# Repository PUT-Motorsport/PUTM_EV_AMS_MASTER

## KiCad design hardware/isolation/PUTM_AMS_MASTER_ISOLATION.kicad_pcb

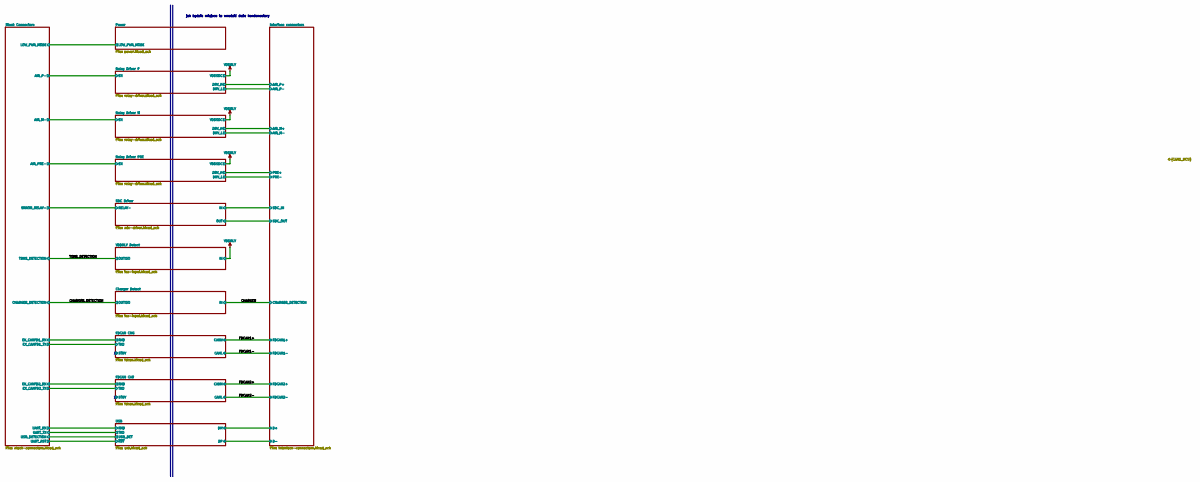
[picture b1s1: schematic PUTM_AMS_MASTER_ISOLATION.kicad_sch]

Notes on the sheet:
jak będzie miejsce to wsadzić duże kondensatory

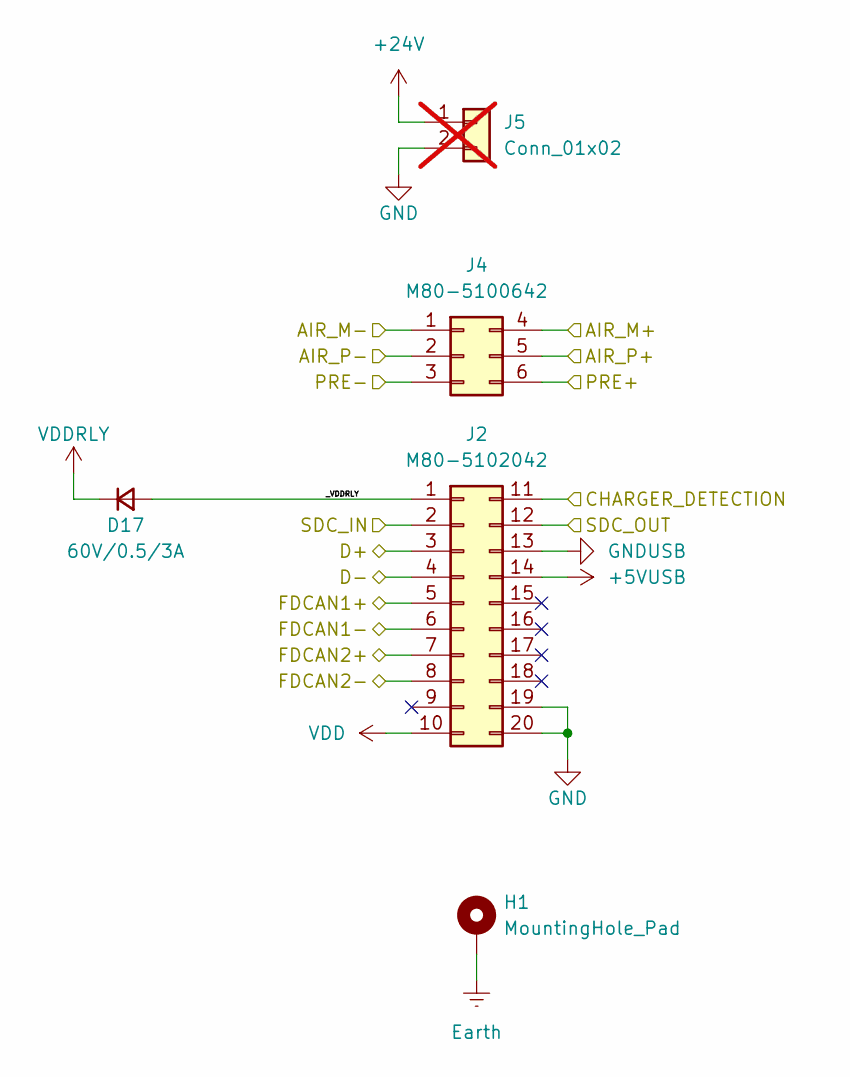
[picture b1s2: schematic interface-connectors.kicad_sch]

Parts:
D17: 60V/0.5/3A; D_SOD-123; Mouser Part Number 637-SKL36
H1: MountingHole_Pad; MountingHole_3.2mm_M3_Pad_Via
J2: M80-5102042; M80-51020YY; Mouser Part Number 855-M80-5102042
J4: M80-5100642; M80-51006YY; Mouser Part Number 855-M80-5100642
J5: Conn_01x02; PinHeader_1x02_P2.00mm_Vertical; not fitted

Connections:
+5VUSB: J2.14; also elsewhere on the board
+24V: J5.1; also elsewhere on the board
/CHARGER: J2.11; also elsewhere on the board
/FDCAN1+: J2.5; also elsewhere on the board
/FDCAN1-: J2.6; also elsewhere on the board
/FDCAN2+: J2.7; also elsewhere on the board
/FDCAN2-: J2.8; also elsewhere on the board
/Interface connectors/AIR_M+: J4.4; also elsewhere on the board
/Interface connectors/AIR_M-: J4.1; also elsewhere on the board
/Interface connectors/AIR_P+: J4.5; also elsewhere on the board
/Interface connectors/AIR_P-: J4.2; also elsewhere on the board
/Interface connectors/D+: J2.3; also elsewhere on the board
/Interface connectors/D-: J2.4; also elsewhere on the board
/Interface connectors/PRE+: J4.6; also elsewhere on the board
/Interface connectors/PRE-: J4.3; also elsewhere on the board
/Interface connectors/SDC_IN: J2.2; also elsewhere on the board
/Interface connectors/SDC_OUT: J2.12; also elsewhere on the board
/Interface connectors/_VDDRLY: D17.2 (A), J2.1
GND: J2.19, J2.20, J5.2; also elsewhere on the board
GNDUSB: J2.13; also elsewhere on the board
VDD: J2.10; also elsewhere on the board
VDDRLY: D17.1 (K); also elsewhere on the board

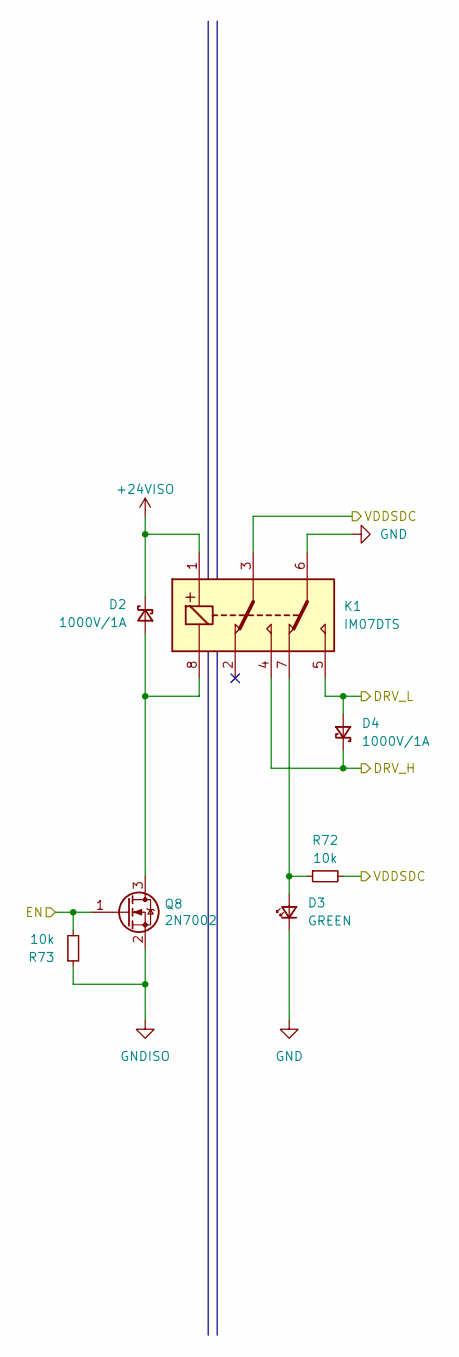
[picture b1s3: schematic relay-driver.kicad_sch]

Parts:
D2, D4: 1000V/1A; D_SOD-123; Mouser Part Number 863-NRVS1MFL
D3: GREEN; D_0603_1608Metric
K1: IM07DTS; IM23TS; Mouser Part Number 655-IM07DTS
Q8: 2N7002; SOT-23; Manufacturer_Part_Number --; Mouser Part Number 621-DMN65D8L-7
R72, R73: 10k; R_0603_1608Metric; Manufacturer_Part_Number --; Mouser Part Number --

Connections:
+24VISO: D2.1 (K), K1.1 (COIL_1); also elsewhere on the board
/Interface connectors/AIR_P+: D4.1 (K), K1.4 (NO_1); also elsewhere on the board
/Interface connectors/AIR_P-: D4.2 (A), K1.5 (NO_2); also elsewhere on the board
/Relay Driver P/EN: Q8.1 (G), R73.2; also elsewhere on the board
GND: D3.1 (K), K1.6 (COM_2); also elsewhere on the board
GNDISO: Q8.2 (S), R73.1; also elsewhere on the board
unnamed: D2.2 (A), K1.8 (COIL_2), Q8.3 (D)
unnamed: D3.2 (A), K1.7 (NC_2), R72.1
VDDRLY: K1.3 (COM_1), R72.2; also elsewhere on the board

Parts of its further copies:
D12, D15: GREEN; D_0603_1608Metric
K3, K4: IM07DTS; IM23TS; Mouser Part Number 655-IM07DTS
Q9, Q10: 2N7002; SOT-23; Manufacturer_Part_Number --; Mouser Part Number 621-DMN65D8L-7
R74, R83, R84, R85: 10k; R_0603_1608Metric; Manufacturer_Part_Number --; Mouser Part Number --

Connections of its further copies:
+24VISO: K3.1 (COIL_1), K4.1 (COIL_1); also elsewhere on the board
/Interface connectors/AIR_M+: K3.4 (NO_1); also elsewhere on the board
/Interface connectors/AIR_M-: K3.5 (NO_2); also elsewhere on the board
/Interface connectors/PRE+: K4.4 (NO_1); also elsewhere on the board
/Interface connectors/PRE-: K4.5 (NO_2); also elsewhere on the board
/Relay Driver M/EN: Q9.1 (G), R74.2; also elsewhere on the board
/Relay Driver PRE/EN: Q10.1 (G), R84.2; also elsewhere on the board
GND: D12.1 (K), D15.1 (K), K3.6 (COM_2), K4.6 (COM_2); also elsewhere on the board
GNDISO: Q9.2 (S), Q10.2 (S), R74.1, R84.1; also elsewhere on the board
unnamed 82: K3.8 (COIL_2), Q9.3 (D); also elsewhere on the board
unnamed: D12.2 (A), K3.7 (NC_2), R83.1
unnamed 84: K4.8 (COIL_2), Q10.3 (D); also elsewhere on the board
unnamed: D15.2 (A), K4.7 (NC_2), R85.1
VDDRLY: K3.3 (COM_1), K4.3 (COM_1), R83.2, R85.2; also elsewhere on the board

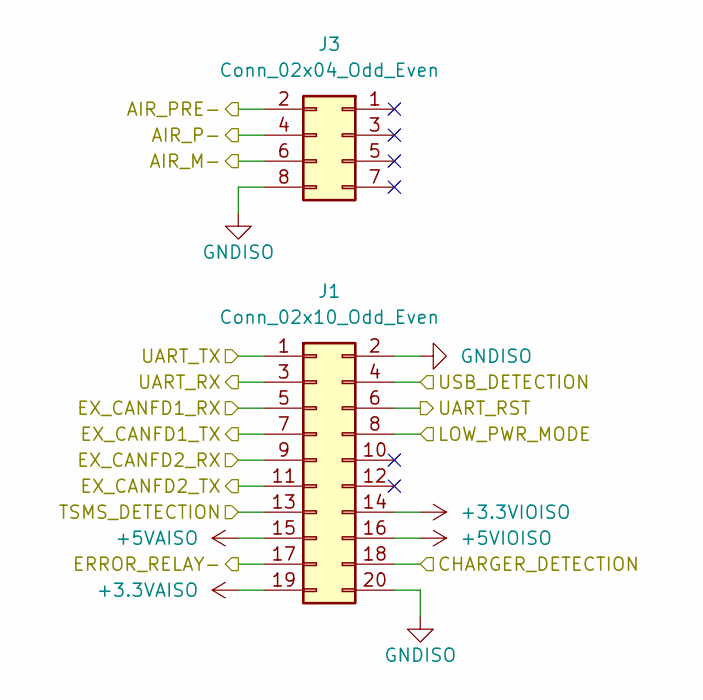
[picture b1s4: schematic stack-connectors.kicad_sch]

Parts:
J1: Conn_02x10_Odd_Even; PinSocket_2x10_P2.00mm_Vertical; Mouser Part Number 200-SQT12001LD
J3: Conn_02x04_Odd_Even; PinSocket_2x04_P2.00mm_Vertical; Mouser Part Number 200-SQT10801LD

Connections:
+3.3VAISO: J1.19; also elsewhere on the board
+3.3VIOISO: J1.14; also elsewhere on the board
+5VAISO: J1.15; also elsewhere on the board
+5VIOISO: J1.16; also elsewhere on the board
/CHARGER_DETECTION: J1.18; also elsewhere on the board
/FDCAN CAR/RXD: J1.9; also elsewhere on the board
/FDCAN CAR/TXD: J1.11; also elsewhere on the board
/FDCAN CHG/RXD: J1.5; also elsewhere on the board
/FDCAN CHG/TXD: J1.7; also elsewhere on the board
/Power/LOW_PWR_MODE: J1.8; also elsewhere on the board
/Relay Driver M/EN: J3.6; also elsewhere on the board
/Relay Driver P/EN: J3.4; also elsewhere on the board
/Relay Driver PRE/EN: J3.2; also elsewhere on the board
/SDC Driver/RELAY-: J1.17; also elsewhere on the board
/Stack Connectors/UART_RST: J1.6; also elsewhere on the board
/Stack Connectors/UART_RX: J1.3; also elsewhere on the board
/Stack Connectors/UART_TX: J1.1; also elsewhere on the board
/Stack Connectors/USB_DETECTION: J1.4; also elsewhere on the board
/TSMS_DETECTION: J1.13; also elsewhere on the board
GNDISO: J1.2, J1.20, J3.8; also elsewhere on the board

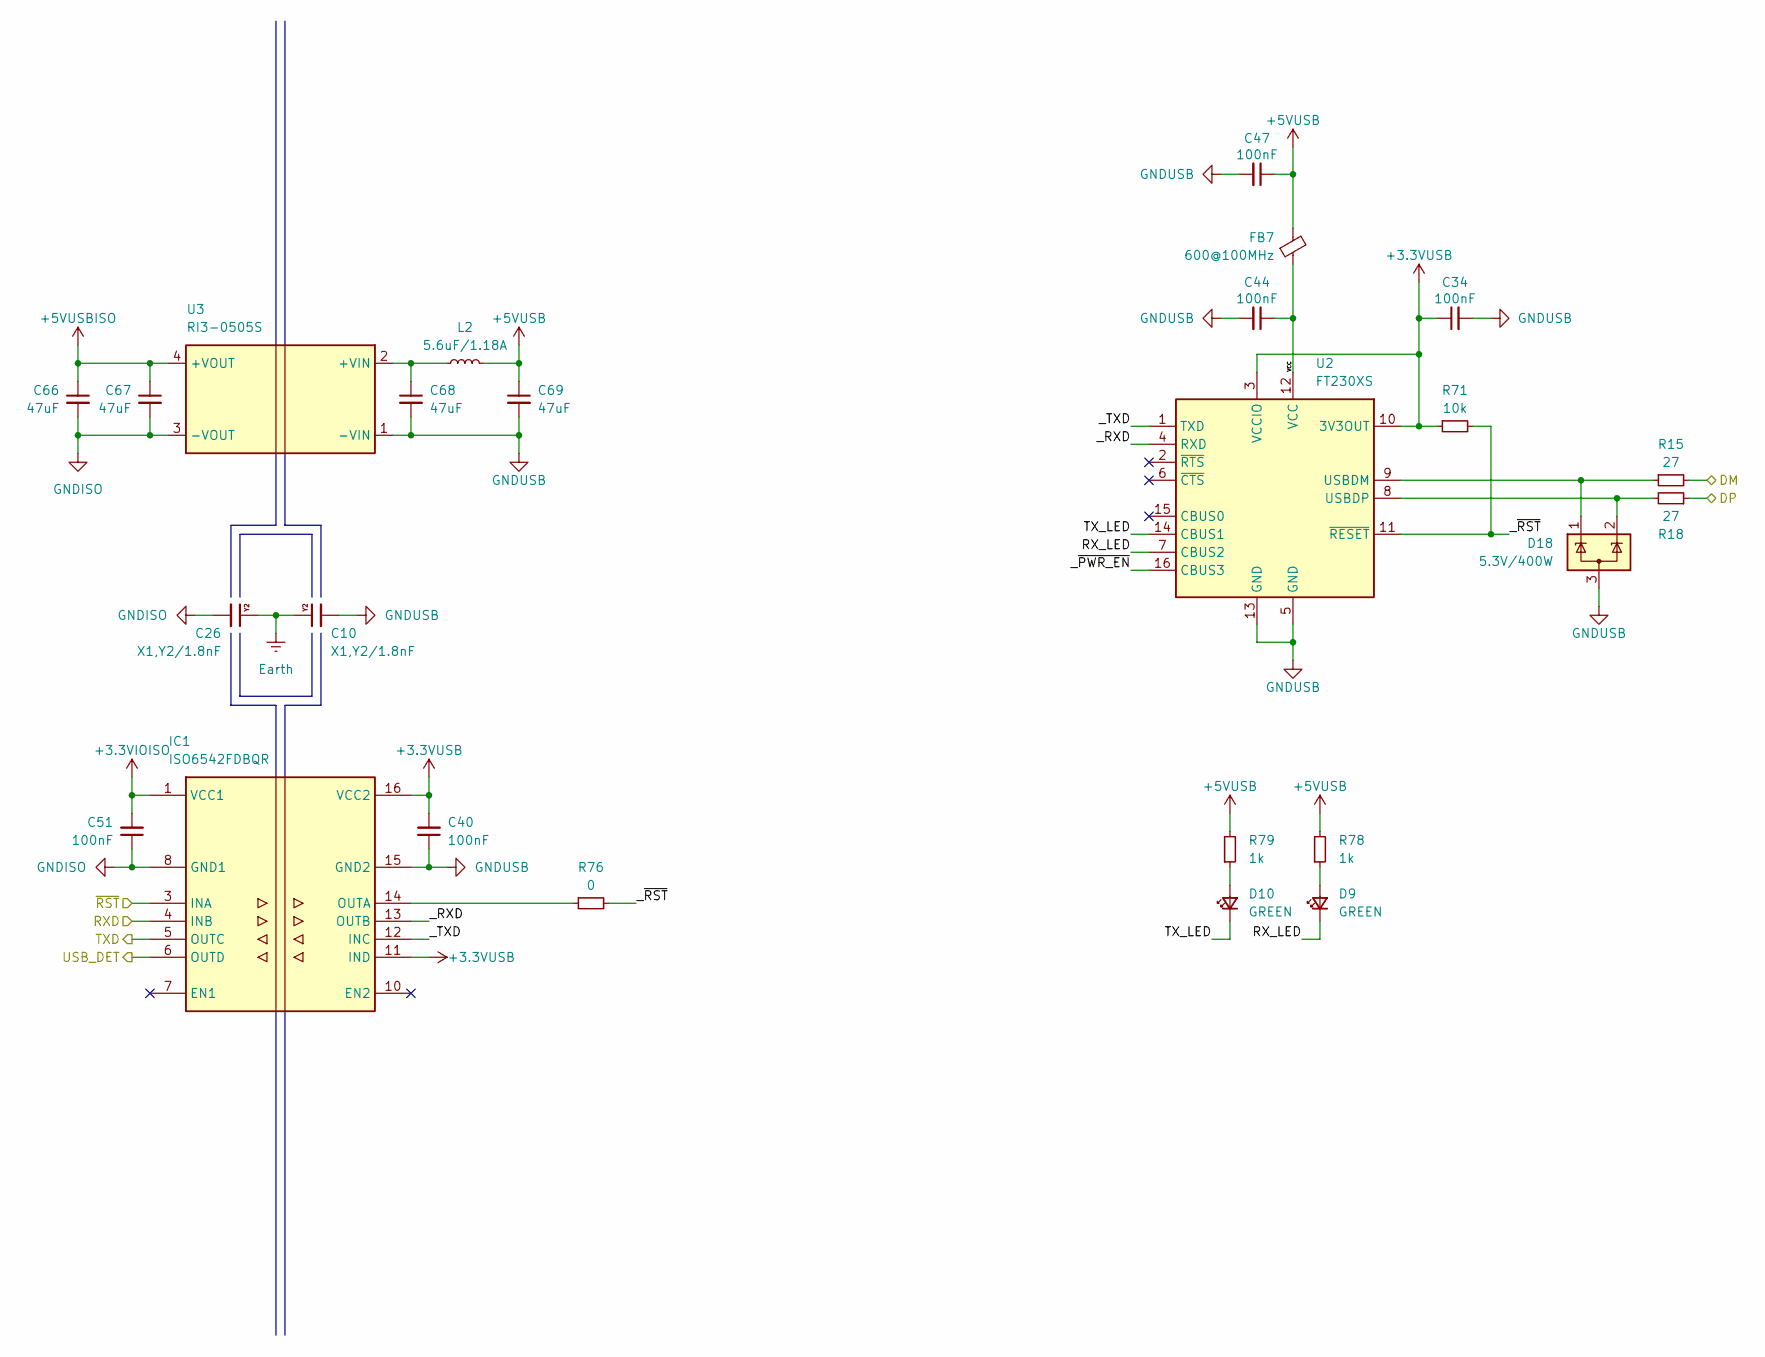
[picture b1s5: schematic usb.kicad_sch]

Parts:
C10, C26: X1,Y2/1.8nF; CAPC5728X280N; Mouser Part Number 80-CAS21C222KARFC
C34, C40, C44, C47, C51: 100nF; C_0603_1608Metric; Manufacturer_Part_Number --; Mouser Part Number --
C66, C67, C68, C69: 47uF; C_0805_2012Metric; Mouser Part Number 81-GRM21BR61A476ME5L
D9, D10: GREEN; D_0603_1608Metric
D18: 5.3V/400W; SOT-23-3; Mouser Part Number 511-ESDA5V3L
FB7: 600@100MHz; L_0805_2012Metric
IC1: ISO6542FDBQR; SSOP-16_3.9x4.9mm_P0.635mm; Mouser Part Number 595-ISO6542FDBQR
L2: 5.6uF/1.18A; RLS567; Mouser Part Number RLS-567-R
R15, R18: 27; R_0603_1608Metric; Manufacturer_Part_Number --; Mouser Part Number 71-CRCW060333R0FKEC
R71: 10k; R_0603_1608Metric; Manufacturer_Part_Number --; Mouser Part Number --
R76: 0; R_0603_1608Metric; Manufacturer_Part_Number --; Mouser Part Number --
R78, R79: 1k; R_0603_1608Metric; Manufacturer_Part_Number --; Mouser Part Number --
U2: FT230XS; SSOP-16_3.9x4.9mm_P0.635mm; Mouser Part Number 895-FT230XS-R
U3: RI3-0505S; RI30505S; Mouser Part Number 919-RI3-0505S

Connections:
+3.3VIOISO: C51.2, IC1.1 (VCC1); also elsewhere on the board
+3.3VUSB: C34.1, C40.2, IC1.11 (IND), IC1.16 (VCC2), R71.1, U2.3 (VCCIO), U2.10 (3V3OUT)
+5VUSB: C47.1, C69.1, FB7.2, L2.2, R78.2, R79.2; also elsewhere on the board
+5VUSBISO: C66.1, C67.1, U3.4 (+VOUT); also elsewhere on the board
/Interface connectors/D+: R15.2; also elsewhere on the board
/Interface connectors/D-: R18.1; also elsewhere on the board
/Stack Connectors/UART_RST: IC1.3 (INA); also elsewhere on the board
/Stack Connectors/UART_RX: IC1.4 (INB); also elsewhere on the board
/Stack Connectors/UART_TX: IC1.5 (OUTC); also elsewhere on the board
/Stack Connectors/USB_DETECTION: IC1.6 (OUTD); also elsewhere on the board
/USB/RX_LED: D9.1 (K), U2.7 (CBUS2)
/USB/TX_LED: D10.1 (K), U2.14 (CBUS1)
/USB/VCC: C44.1, FB7.1, U2.12 (VCC)
/USB/_RXD: IC1.13 (OUTB), U2.4 (RXD)
/USB/_TXD: IC1.12 (INC), U2.1 (TXD)
/USB/_~PWR_EN: U2.16 (CBUS3)
/USB/_~RST: R71.2, R76.2, U2.11 (~RESET)
Earth: C10.1, C26.1; also elsewhere on the board
GNDISO: C26.2, C51.1, C66.2, C67.2, IC1.2 (GND1), IC1.8 (GND1), U3.3 (-VOUT); also elsewhere on the board
GNDUSB: C10.2, C34.2, C40.1, C44.2, C47.2, C68.2, C69.2, D18.3 (A), IC1.9 (GND2), IC1.15 (GND2), U2.5 (GND), U2.13 (GND), U3.1 (-VIN); also elsewhere on the board
unnamed: D9.2 (A), R78.1
unnamed: D10.2 (A), R79.1
unnamed: IC1.14 (OUTA), R76.1
unnamed: D18.1 (K), R15.1, U2.9 (USBDM)
unnamed: D18.2 (K), R18.2, U2.8 (USBDP)
unnamed: C68.1, L2.1, U3.2 (+VIN)

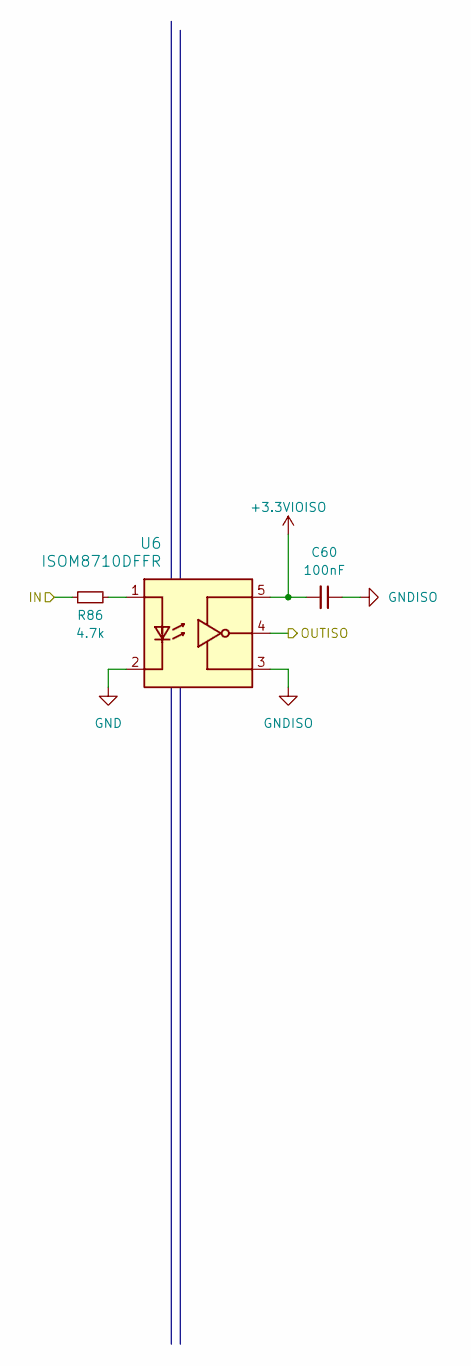
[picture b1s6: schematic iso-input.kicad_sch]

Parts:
C60: 100nF; C_0603_1608Metric
R86: 4.7k; R_0603_1608Metric; Manufacturer_Part_Number --; Mouser Part Number --
U6: ISOM8710DFFR; DFF0005A-C01-MFG

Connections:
+3.3VIOISO: C60.2, U6.5 (VDD); also elsewhere on the board
/TSMS_DETECTION: U6.4 (VO); also elsewhere on the board
GND: U6.2 (K); also elsewhere on the board
GNDISO: C60.1, U6.3 (GND); also elsewhere on the board
unnamed: R86.2, U6.1 (A)
VDDRLY: R86.1; also elsewhere on the board

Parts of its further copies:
C65: 100nF; C_0603_1608Metric
R88: 4.7k; R_0603_1608Metric; Manufacturer_Part_Number --; Mouser Part Number --
U7: ISOM8710DFFR; DFF0005A-C01-MFG

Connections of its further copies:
+3.3VIOISO: C65.2, U7.5 (VDD); also elsewhere on the board
/CHARGER: R88.1; also elsewhere on the board
/CHARGER_DETECTION: U7.4 (VO); also elsewhere on the board
GND: U7.2 (K); also elsewhere on the board
GNDISO: C65.1, U7.3 (GND); also elsewhere on the board
unnamed: R88.2, U7.1 (A)

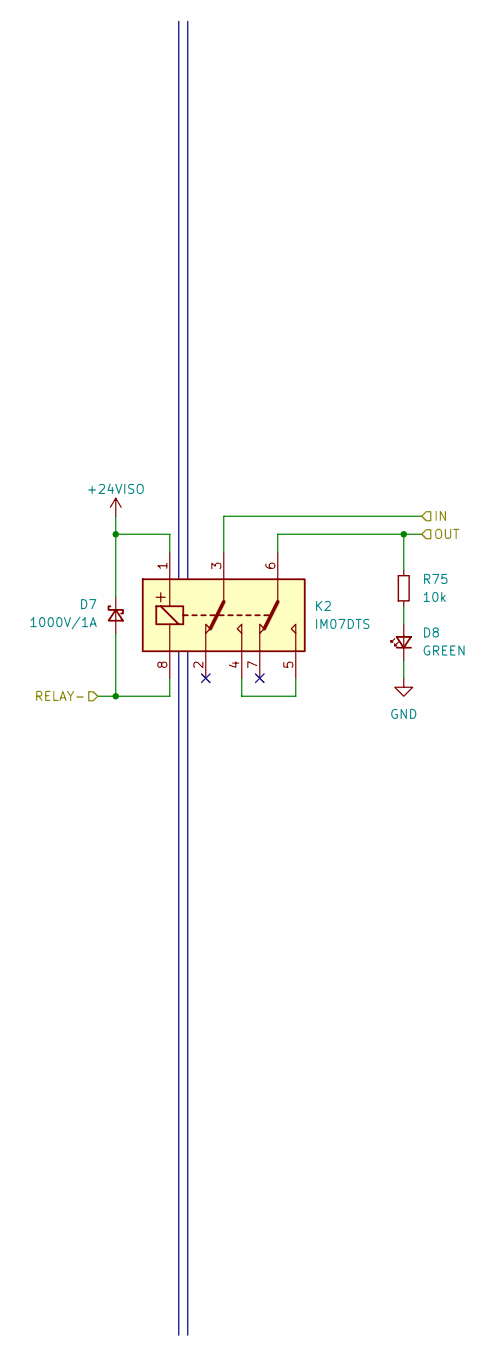
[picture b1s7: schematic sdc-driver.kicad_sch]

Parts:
D7: 1000V/1A; D_SOD-123; Mouser Part Number 863-NRVS1MFL
D8: GREEN; D_0603_1608Metric
K2: IM07DTS; IM23TS; Mouser Part Number 655-IM07DTS
R75: 10k; R_0603_1608Metric; Manufacturer_Part_Number --; Mouser Part Number --

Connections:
+24VISO: D7.1 (K), K2.1 (COIL_1); also elsewhere on the board
/Interface connectors/SDC_IN: K2.3 (COM_1); also elsewhere on the board
/Interface connectors/SDC_OUT: K2.6 (COM_2), R75.2; also elsewhere on the board
/SDC Driver/RELAY-: D7.2 (A), K2.8 (COIL_2); also elsewhere on the board
GND: D8.1 (K); also elsewhere on the board
unnamed: D8.2 (A), R75.1
unnamed: K2.4 (NO_1), K2.5 (NO_2)

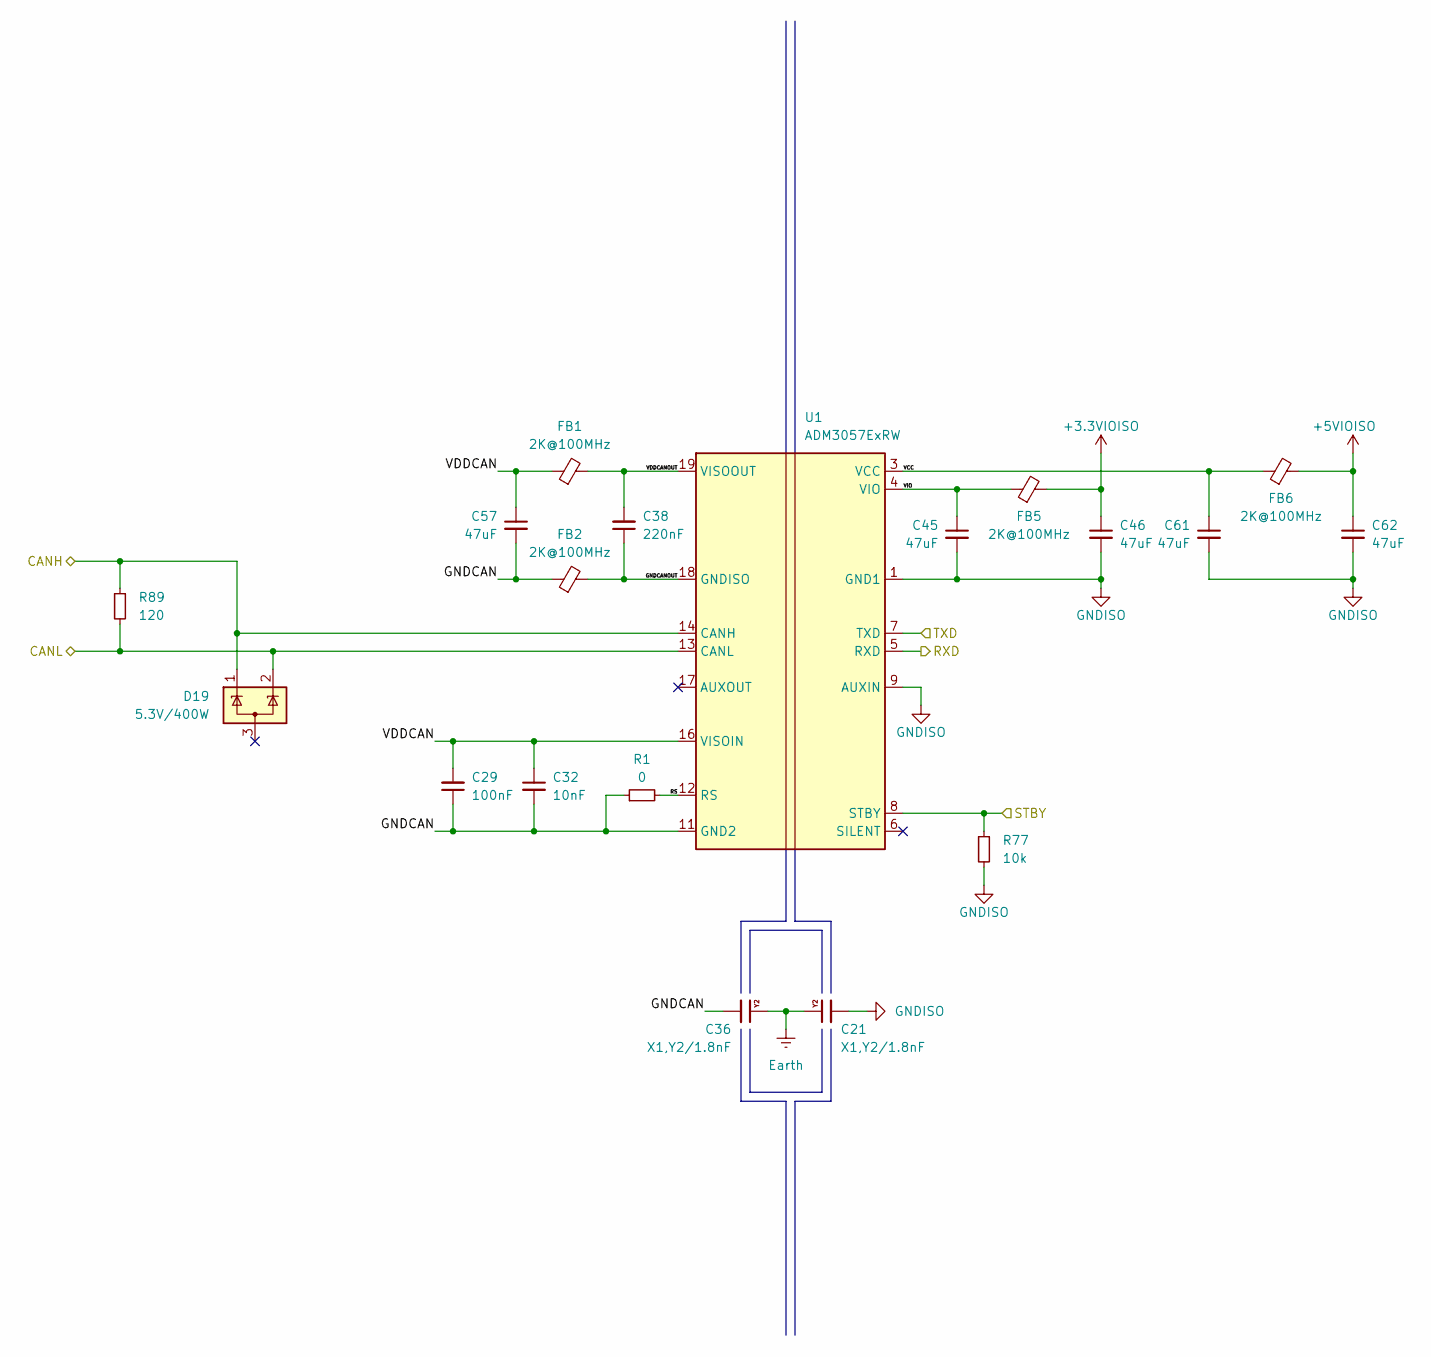
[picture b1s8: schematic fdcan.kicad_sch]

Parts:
C21, C36: X1,Y2/1.8nF; CAPC5728X280N; Mouser Part Number 80-CAS21C222KARFC
C29: 100nF; C_0603_1608Metric
C32: 10nF; C_0603_1608Metric
C38: 220nF; C_0603_1608Metric
C45, C46, C57, C61, C62: 47uF; C_0805_2012Metric; Mouser Part Number 81-GRM21BR61A476ME5L
D19: 5.3V/400W; SOT-23-3; Mouser Part Number 511-ESDA5V3L
FB1, FB2, FB5, FB6: 2K@100MHz; L_0805_2012Metric; Mouser Part Number 623-2508052027Y1
R1: 0; R_0603_1608Metric; Mouser Part Number --
R77: 10k; R_0603_1608Metric; Manufacturer_Part_Number --; Mouser Part Number --
R89: 120; R_0603_1608Metric; Manufacturer_Part_Number --; Mouser Part Number --
U1: ADM3057ExRW; SOIC-20W_7.5x12.8mm_P1.27mm

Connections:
+3.3VIOISO: C46.1, FB5.2; also elsewhere on the board
+5VIOISO: C62.1, FB6.2; also elsewhere on the board
/FDCAN2+: D19.1 (K), R89.1, U1.14 (CANH); also elsewhere on the board
/FDCAN2-: D19.2 (K), R89.2, U1.13 (CANL); also elsewhere on the board
/FDCAN CAR/GNDCAN: C29.1, C32.2, C36.2, C57.2, FB2.1, R1.1, U1.11 (GND2), U1.15 (GND2)
/FDCAN CAR/GNDCANOUT: C38.1, FB2.2, U1.18 (GNDISO), U1.20 (GNDISO)
/FDCAN CAR/RS: R1.2, U1.12 (RS)
/FDCAN CAR/RXD: U1.5 (RXD); also elsewhere on the board
/FDCAN CAR/STBY: R77.1, U1.8 (STBY)
/FDCAN CAR/TXD: U1.7 (TXD); also elsewhere on the board
/FDCAN CAR/VCC: C61.1, FB6.1, U1.3 (VCC)
/FDCAN CAR/VDDCAN: C29.2, C32.1, C57.1, FB1.1, U1.16 (VISOIN)
/FDCAN CAR/VDDCANOUT: C38.2, FB1.2, U1.19 (VISOOUT)
/FDCAN CAR/VIO: C45.1, FB5.1, U1.4 (VIO)
Earth: C21.1, C36.1; also elsewhere on the board
GNDISO: C21.2, C45.2, C46.2, C61.2, C62.2, R77.2, U1.1 (GND1), U1.2 (GND1), U1.9 (AUXIN), U1.10 (GND1); also elsewhere on the board

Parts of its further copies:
C22, C56: X1,Y2/1.8nF; CAPC5728X280N; Mouser Part Number 80-CAS21C222KARFC
C41: 220nF; C_0603_1608Metric
C50, C58, C59, C63, C64: 47uF; C_0805_2012Metric; Mouser Part Number 81-GRM21BR61A476ME5L
C54: 100nF; C_0603_1608Metric
C55: 10nF; C_0603_1608Metric
D20: 5.3V/400W; SOT-23-3; Mouser Part Number 511-ESDA5V3L
FB3, FB4, FB8, FB9: 2K@100MHz; L_0805_2012Metric; Mouser Part Number 623-2508052027Y1
R2: 0; R_0603_1608Metric; Mouser Part Number --
R87: 10k; R_0603_1608Metric; Manufacturer_Part_Number --; Mouser Part Number --
R90: 120; R_0603_1608Metric; Manufacturer_Part_Number --; Mouser Part Number --
U5: ADM3057ExRW; SOIC-20W_7.5x12.8mm_P1.27mm

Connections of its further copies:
+3.3VIOISO: C50.1, FB8.2; also elsewhere on the board
+5VIOISO: C64.1, FB9.2; also elsewhere on the board
/FDCAN1+: D20.1 (K), R90.1, U5.14 (CANH); also elsewhere on the board
/FDCAN1-: D20.2 (K), R90.2, U5.13 (CANL); also elsewhere on the board
/FDCAN CHG/GNDCAN: C54.1, C55.2, C56.2, C59.2, FB4.1, R2.1, U5.11 (GND2), U5.15 (GND2)
/FDCAN CHG/GNDCANOUT: C41.1, FB4.2, U5.18 (GNDISO), U5.20 (GNDISO)
/FDCAN CHG/RS: R2.2, U5.12 (RS)
/FDCAN CHG/RXD: U5.5 (RXD); also elsewhere on the board
/FDCAN CHG/STBY: R87.1, U5.8 (STBY)
/FDCAN CHG/TXD: U5.7 (TXD); also elsewhere on the board
/FDCAN CHG/VCC: C63.1, FB9.1, U5.3 (VCC)
/FDCAN CHG/VDDCAN: C54.2, C55.1, C59.1, FB3.1, U5.16 (VISOIN)
/FDCAN CHG/VDDCANOUT: C41.2, FB3.2, U5.19 (VISOOUT)
/FDCAN CHG/VIO: C58.1, FB8.1, U5.4 (VIO)
Earth: C22.1, C56.1; also elsewhere on the board
GNDISO: C22.2, C50.2, C58.2, C63.2, C64.2, R87.2, U5.1 (GND1), U5.2 (GND1), U5.9 (AUXIN), U5.10 (GND1); also elsewhere on the board

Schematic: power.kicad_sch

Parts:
C1, C6, C7, C8: X1,Y2/1.8nF; CAPC5728X280N; Mouser Part Number 80-CAS26C182KARFC
C2, C3, C4, C5, C9, C11, C12, C13: 4.7uF; C_1812_4532Metric; Mouser Part Number 581-KGM43JR72A475KV
C14, C15, C16, C17: 2.2uF; C_0603_1608Metric; Manufacturer_Part_Number GRT188R61H225KE13
C30, C31, C33, C37, C39, C42: 22uF; C_0805_2012Metric; Manufacturer_Part_Number CL21A107MQYNNWE; Mouser Part Number 810-C2012X5R1V226MAC
C43, C48, C49: 100nF; C_0603_1608Metric; Manufacturer_Part_Number --; Mouser Part Number --
D1: 30V/600W; D_SOD-123; Mouser Part Number 576-SZSMF6L28CAT3G
D5: 10V; D_SOD-123; Mouser Part Number 863-MMSZ5240BT1G
D6: GREEN; D_0603_1608Metric
F2: 5A/24V; Fuse_2920_7451Metric; Mouser Part Number 576-2920L500/24SLDR
F5, F6: 5V/0.5A; Fuse_0805_2012Metric; Manufacturer_Part_Number 0ZCH0050FF2G; Mouser Part Number 530-0ZCH0050FF2G
FL1: 701@100MHz; ACM55V7012PLTL00; Mouser Part Number 810-ACM55V7012PLTL00
IC4: LMZM23601V5SILT; Mouser Part Number 595-LMZM23601V5SILT
IC6, IC7: 3.3V/0.5A; SOT-23-5; Mouser Part Number 595-TPS7B92033DBVR
L3: 5.6uF/1.18A; RLS567; Mouser Part Number RLS-567-R
PS2: EC5DAW-24D12N; EC5DAW24D12N; Manufacturer_Part_Number EC5DAW-24D12N
Q4: SI2347DS-T1-GE3; SOT-23-3
R10: 100k; R_0603_1608Metric; Mouser Part Number --
R11: 510; R_0603_1608Metric; Mouser Part Number --
R16: 20k; R_0603_1608Metric
R39: 100k; R_0603_1608Metric; Manufacturer_Part_Number RT0603DRE07100KL; Mouser Part Number --
R40: 400; R_0603_1608Metric; Manufacturer_Part_Number RT0603DRE07100KL; Mouser Part Number --
R82: 10k; R_0603_1608Metric; Manufacturer_Part_Number --; Mouser Part Number --
U4: TPS2113PWR; TSSOP-8_4.4x3mm_P0.65mm; Mouser Part Number 595-TPS2113PWR

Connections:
+3.3VAISO: F6.2; also elsewhere on the board
+3.3VIOISO: F5.2, R82.2; also elsewhere on the board
+5VAISO: C16.2, C42.2, IC7.1 (VI), L3.2; also elsewhere on the board
+5VIOISO: C15.2, C39.2, C49.2, IC6.1 (VI), L3.1, R11.2, U4.7 (OUT); also elsewhere on the board
+5VISO: C33.2, C37.2, C43.2, IC4.6 (VOUT), IC4.7 (FB), R39.1, U4.8 (IN1)
+5VUSBISO: C48.2, U4.6 (IN2); also elsewhere on the board
+24V: C4.1, C5.1, D5.1 (K), FL1.1, Q4.2 (S); also elsewhere on the board
+24VISO: C8.2, C9.1, C12.1, C30.2, C31.2, IC4.3 (VIN), IC4.4 (EN), PS2.9 (+VOUT); also elsewhere on the board
/Power/F_24V: D1.1 (A1), F2.1, Q4.3 (D)
/Power/F_+3.3VA: C17.2, F6.1, IC7.5 (VO)
/Power/F_+3.3VIO: C14.2, F5.1, IC6.5 (VO)
/Power/ILIM: R40.2, U4.4 (ILIM)
/Power/LOW_PWR_MODE: R82.1, U4.1 (STAT); also elsewhere on the board
/Power/PS_+24V: C2.1, C3.1, C7.2, FL1.4, PS2.16 (+VIN)
/Power/PS_GND: C2.2, C3.2, C6.2, FL1.3, PS2.1 (-VIN)
/Power/VSNS: R16.1, R39.2, U4.3 (VSNS)
Earth: C1.1, C6.1, C7.1, C8.1; also elsewhere on the board
GND: C4.2, C5.2, D1.2 (A2), FL1.2, R10.2; also elsewhere on the board
GNDISO: C1.2, C11.2, C13.2, C14.1, C15.1, C16.1, C17.1, C30.1, C31.1, C33.1, C37.1, C39.1, C42.1, C43.1, C48.1, C49.1, D6.1 (K), IC4.1 (GND), IC4.2 (MODE/SYNC), IC4.11 (EP), IC6.2 (GND), IC7.2 (GND), PS2.10 (-VOUT), R16.2, R40.1, U4.2 (~EN), U4.5 (GND); also elsewhere on the board
unnamed: D5.2 (A), Q4.1 (G), R10.1
unnamed: D6.2 (A), R11.1
unnamed: C9.2, C11.1, C12.2, C13.1, PS2.8 (COM)
VDD: F2.2; also elsewhere on the board

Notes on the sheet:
+5VISO has a priority over +5VUSBISO

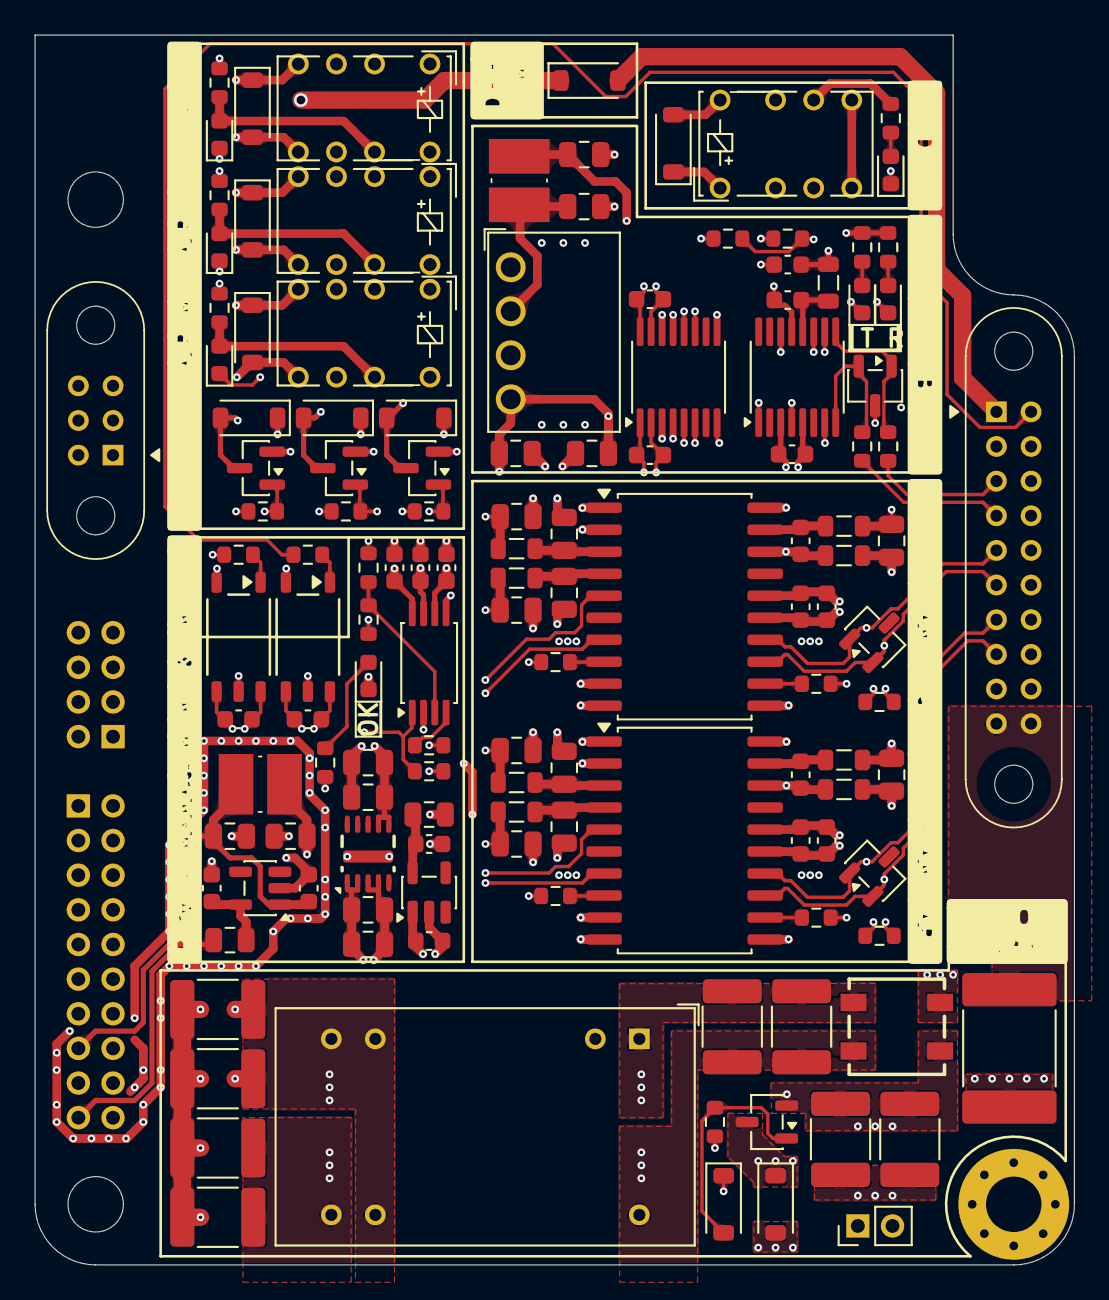
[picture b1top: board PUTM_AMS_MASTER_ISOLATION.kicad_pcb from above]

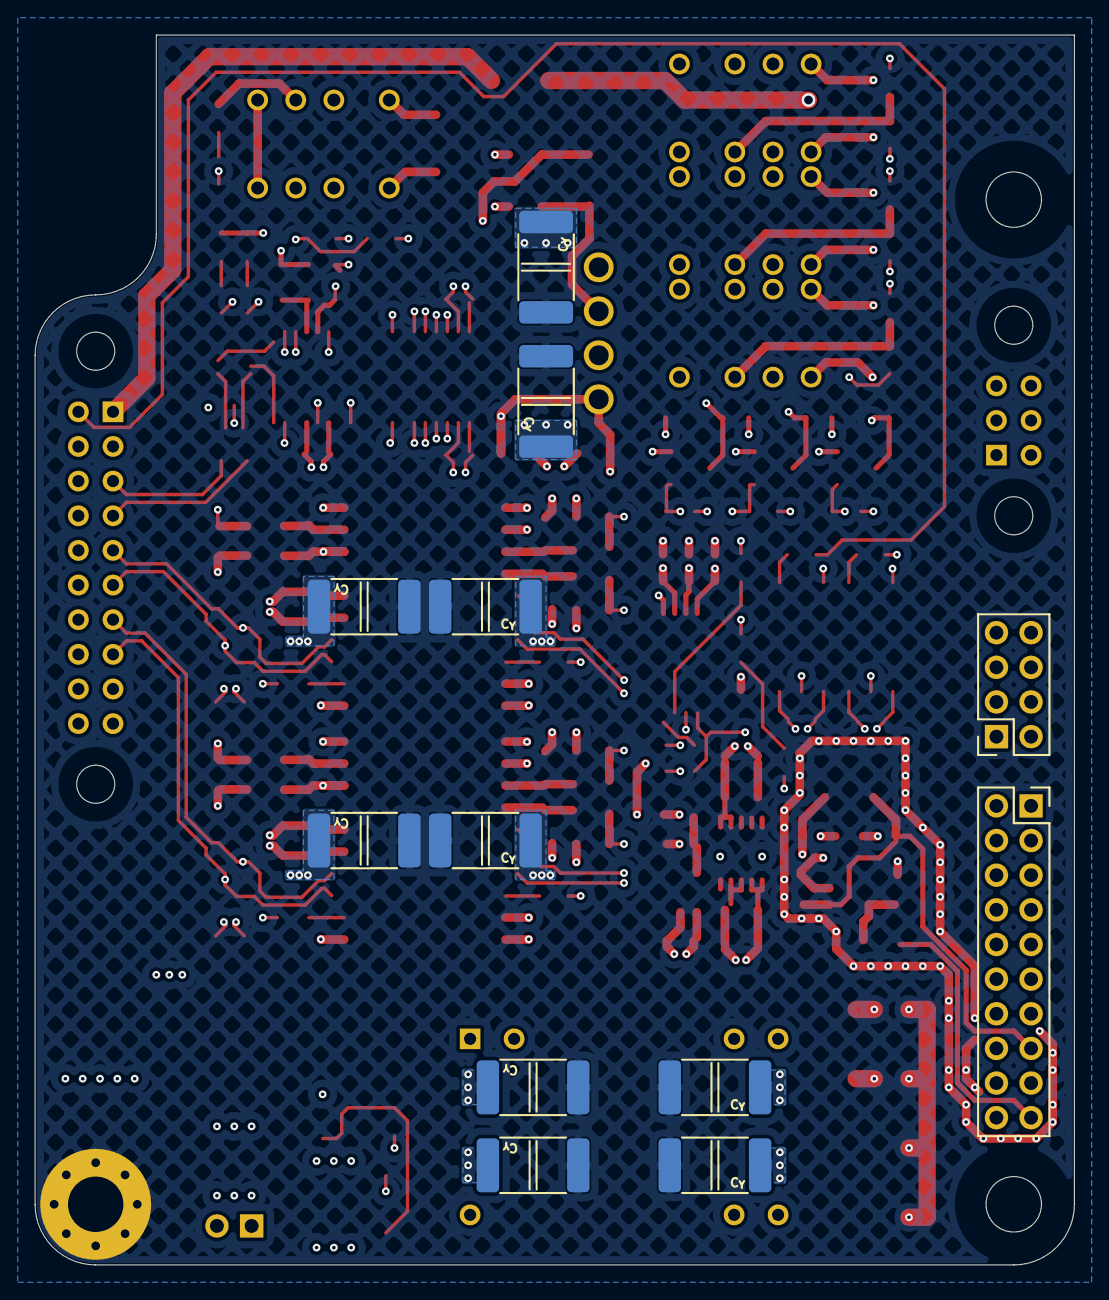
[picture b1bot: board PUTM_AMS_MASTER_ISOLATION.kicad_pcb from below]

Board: 6 copper layers, 60.0 x 71.0 mm, 148 parts (12 on the bottom side), 95 nets.

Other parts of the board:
D11, D13, D14, D16: 30V/4A; D_SOD-123
H1#2: MountingHole_Pad; MountingHole_3.2mm_M3_Pad_Via
H3: M3; MountingHole_3.2mm_M3

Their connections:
+24VISO: D11.1 (K), D14.1 (K); also elsewhere on the board
/Interface connectors/AIR_M+: D13.1 (K); also elsewhere on the board
/Interface connectors/AIR_M-: D13.2 (A); also elsewhere on the board
/Interface connectors/PRE+: D16.1 (K); also elsewhere on the board
/Interface connectors/PRE-: D16.2 (A); also elsewhere on the board
Earth: H1#2.1 (1_1); also elsewhere on the board
unnamed 82: D11.2 (A); also elsewhere on the board
unnamed 84: D14.2 (A); also elsewhere on the board
